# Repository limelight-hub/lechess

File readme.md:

# Lechess
- An early prototyping for smart chess board.

**[Please refer to our planning](https://docs.google.com/spreadsheets/d/1tzjvebM3ZJ8TDiEOB72k3z0SsBjHDWrlPy9oBXgbvGs/edit?gid=1570832848#gid=1570832848)**

****

Figure 1: Hardware block diagram

****

Figure 2: System diagram

# LeChess Functionalities
**1. User Authentication**

    Login: Allows users to log in to the app using their credentials (e.g., email and password). The app sends a request to the NodeJS server, which authenticates the user and provides a JWT token.
    Register: Allows new users to create an account. The account data (username, email, password, etc.) is stored in the NodeJS server and MongoDB.
    Logout: Allows users to log out of the app, clearing their session data.
    Password Reset: Enables users to reset their password via email or SMS by sending a request to the NodeJS server.

**2. Online Mode (App-Only Mode)**

These functions are available when the user is online and connected to the NodeJS server:

*2.1. Play with Computer*

    Start New Game: Users can start a new game against a cloud-based chess engine (e.g., Stockfish).
    Make Move: Users can make a move, and the app sends the move to the NodeJS server to be processed by the chess engine.
    Receive Move: The app receives the move from the chess engine and updates the board.
    Offer Draw/Resign: Users can offer a draw or resign during gameplay.
    Game Over: Displays the result of the game once it's finished (win/loss/draw), and save pgn to database

*2.2. Play with Friend: 2 players*

    Record names of the two players.
    Real-Time Move Updates: The app sends and receives real-time moves from the NodeJS server during a multiplayer game.
    Game Over: Displays the result when the game is finished, and save pgn to database

*2.3. Puzzle Mode*

    Select Puzzle: Users can choose chess puzzles from the server (e.g., checkmate in 2, etc.).
    Solve Puzzle: The app displays the puzzle, and users try to solve it by making moves. The NodeJS server verifies whether the solution is correct.
    Hints: Users can request hints from the server if needed.

*2.4. PGN File Visualization*

    Choose PGN: choose a match from the matches the user played before.
    View PGN: The app reads the PGN file and displays the game on the chessboard for the user to review.
    Step Through Game: Users can move forward and backward.

**3. Bluetooth Mode (Using the Physical Chessboard)**

These functions are available when the user is connected to the physical chessboard via Bluetooth and the Flask server on the Raspberry Pi:

*3.1. Play with Computer* 

    Start New Game: Users can start a new game against a local Stockfish on Raspberry Pi.
    Make Move on Physical Board: The physical chessboard detects the user's move and sends the move to the app over Bluetooth.
    Receive bot Move: The Raspberry Pi processes the move via the chess engine and sends the bot's move back to the app and the physical board and give the pcb led data to light the move up.
    Recommend Move: Moves recommended by the bot will be prcessed to LED data to be lighten up on the board.
    Game Over: Displays the result of the game (win/loss/draw) once it’s finished, and save pgn to database.

*3.2. Play with Friend (Over the Board)*

    Start New Game: Users can start a new game against a friend on the physical chessboard.
    Real-Time Move Detection: The app updates the game state as moves are detected from the chessboard.
    Recommend Move: Moves recommended by the bot will be prcessed to LED data to be lighten up on the board.
    Game Over: Displays the result when the game is finished and saves the game locally on the app or syncs it to the cloud, and save pgn to database.

*3.3. PGN File Visualization*

    Choose PGN: choose a match from a matches list the user have played before using the phone.
    Raspberry Pi server processed PGN and output LED data.
    User can choose to go forward on their phone, or set an automatic mode to go to next move every certain amount of time.

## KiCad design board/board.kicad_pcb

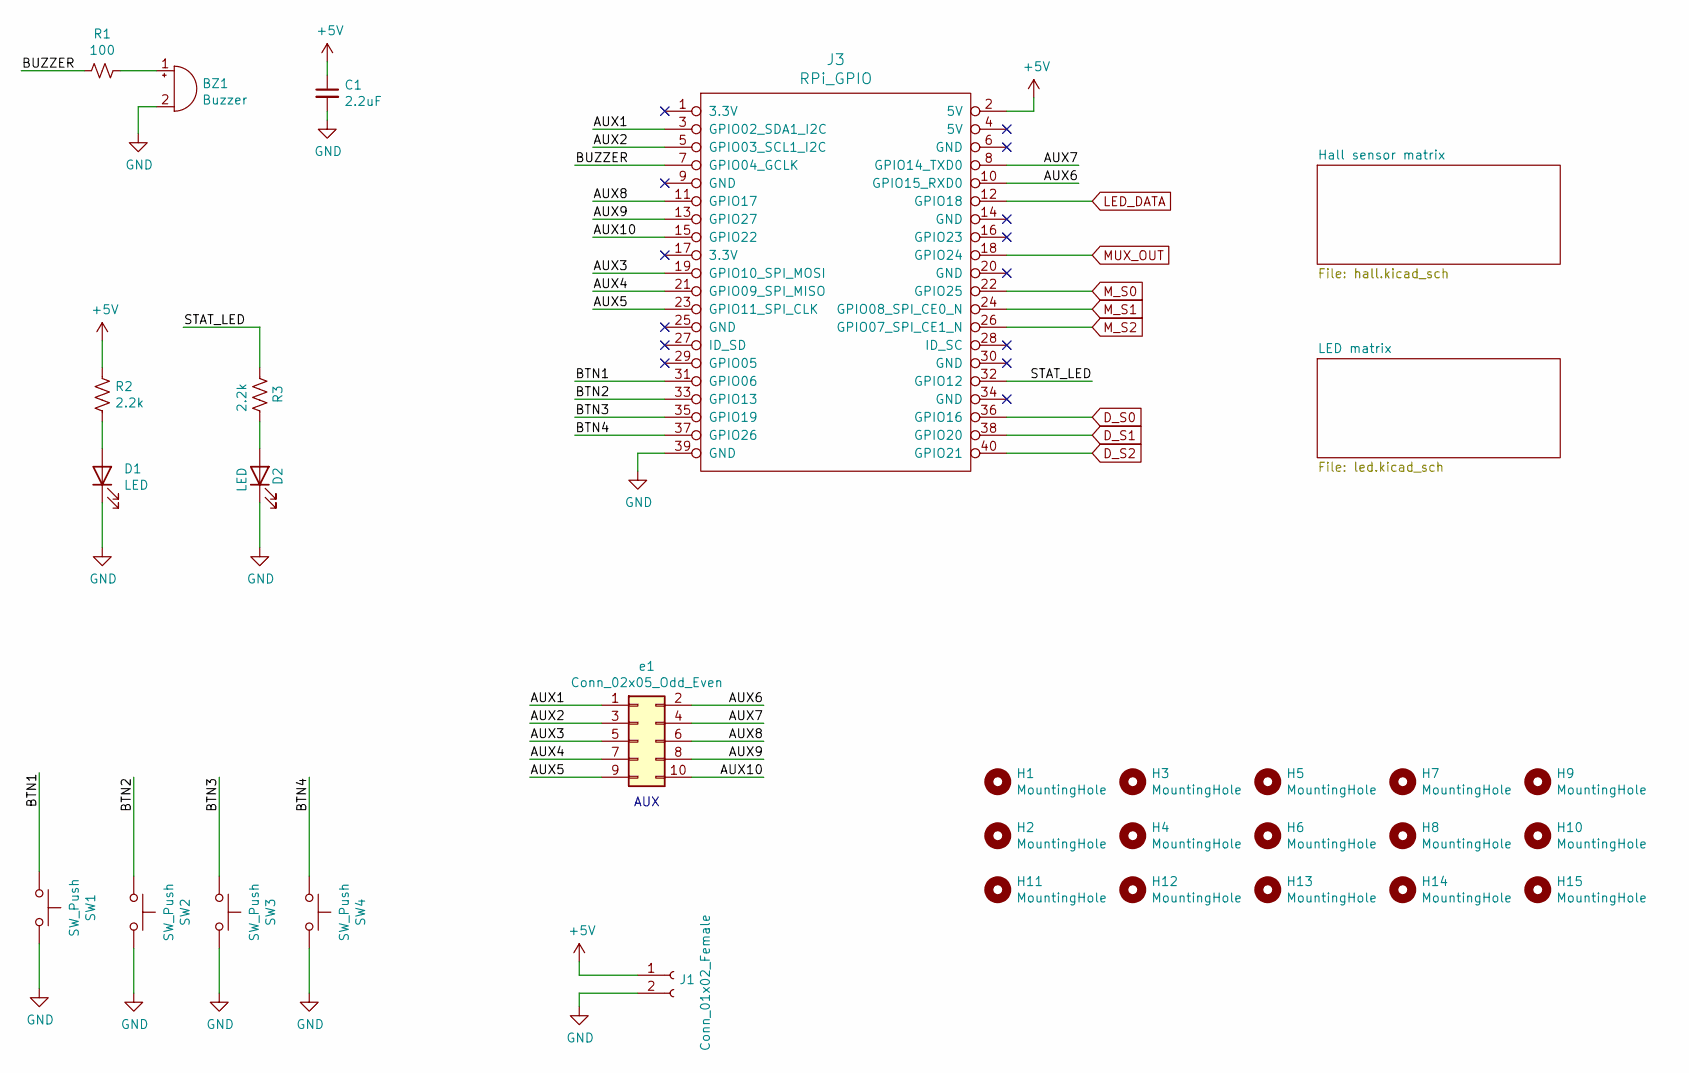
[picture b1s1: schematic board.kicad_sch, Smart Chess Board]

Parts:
BZ1: Buzzer; MagneticBuzzer_ProSignal_ABT-410-RC
C1: 2.2uF; C_0805_2012Metric_Pad1.18x1.45mm_HandSolder
D1, D2: LED; LED_D5.0mm
H1, H2, H3, H4, H5, H6, H7, H8, H9, H10, H11, H12, H13, H14, H15: MountingHole; MountingHole_2.2mm_M2
J1: Conn_01x02_Female; JST_XH_B2B-XH-A_1x02_P2.50mm_Vertical
J3: RPi_GPIO; raspberry_pi_socket
R1: 100; R_Axial_DIN0207_L6.3mm_D2.5mm_P10.16mm_Horizontal
R2, R3: 2.2k; R_Axial_DIN0207_L6.3mm_D2.5mm_P10.16mm_Horizontal
SW1, SW2, SW3, SW4: SW_Push; SW_PUSH_6mm_H5mm
e1: Conn_02x05_Odd_Even; PinSocket_2x05_P2.54mm_Vertical

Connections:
+5V: C1.1, J1.1, J3.2 (5V), R2.1; also elsewhere on the board
/AUX1: J3.3 (GPIO02_SDA1_I2C), e1.1
/AUX2: J3.5 (GPIO03_SCL1_I2C), e1.3
/AUX3: J3.19 (GPIO10_SPI_MOSI), e1.5
/AUX4: J3.21 (GPIO09_SPI_MISO), e1.7
/AUX5: J3.23 (GPIO11_SPI_CLK), e1.9
/AUX6: J3.10 (GPIO15_RXD0), e1.2
/AUX7: J3.8 (GPIO14_TXD0), e1.4
/AUX8: J3.11 (GPIO17), e1.6
/AUX9: J3.13 (GPIO27), e1.8
/AUX10: J3.15 (GPIO22), e1.10
/BTN1: J3.31 (GPIO06), SW1.1
/BTN2: J3.33 (GPIO13), SW2.1
/BTN3: J3.35 (GPIO19), SW3.1
/BTN4: J3.37 (GPIO26), SW4.1
/BUZZER: J3.7 (GPIO04_GCLK), R1.2
/STAT_LED: J3.32 (GPIO12), R3.1
D_S0: J3.36 (GPIO16); also elsewhere on the board
D_S1: J3.38 (GPIO20); also elsewhere on the board
D_S2: J3.40 (GPIO21); also elsewhere on the board
GND: BZ1.2 (+), C1.2, D1.1 (K), D2.1 (K), J1.2, J3.39 (GND), SW1.2, SW2.2, SW3.2, SW4.2; also elsewhere on the board
LED_DATA: J3.12 (GPIO18); also elsewhere on the board
MUX_OUT: J3.18 (GPIO24); also elsewhere on the board
M_S0: J3.22 (GPIO25); also elsewhere on the board
M_S1: J3.24 (GPIO08_SPI_CE0_N); also elsewhere on the board
M_S2: J3.26 (GPIO07_SPI_CE1_N); also elsewhere on the board
unnamed: BZ1.1 (-), R1.1
unnamed: D1.2 (A), R2.2
unnamed: D2.2 (A), R3.2

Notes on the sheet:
AUX

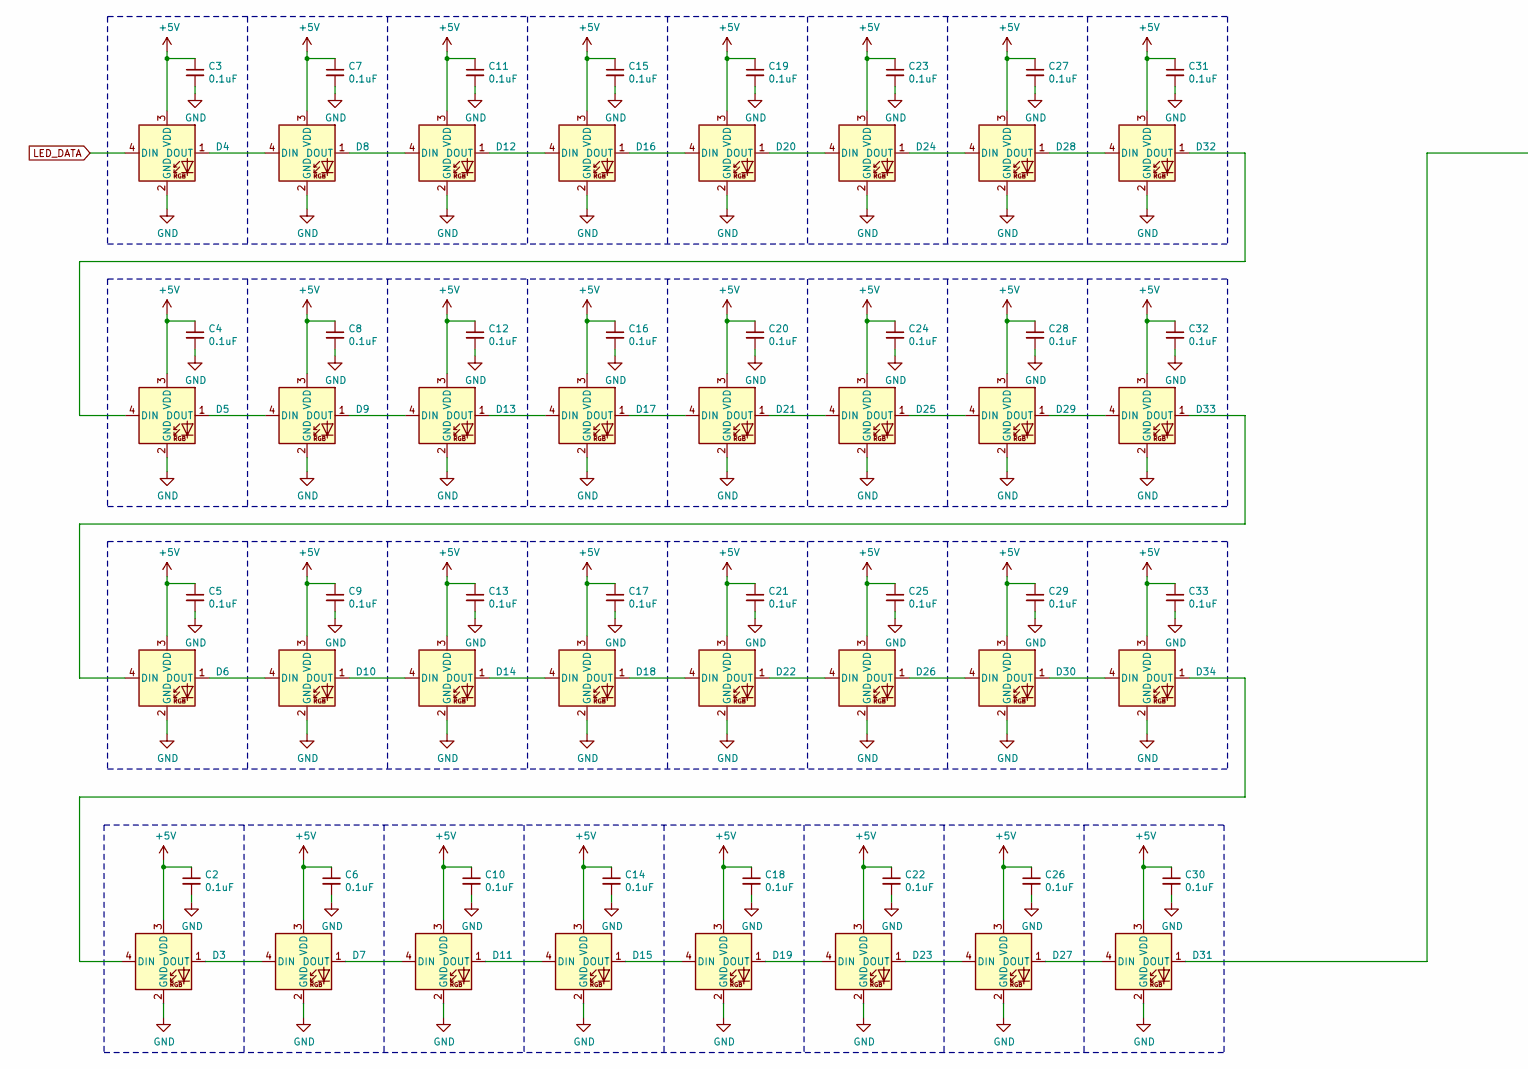
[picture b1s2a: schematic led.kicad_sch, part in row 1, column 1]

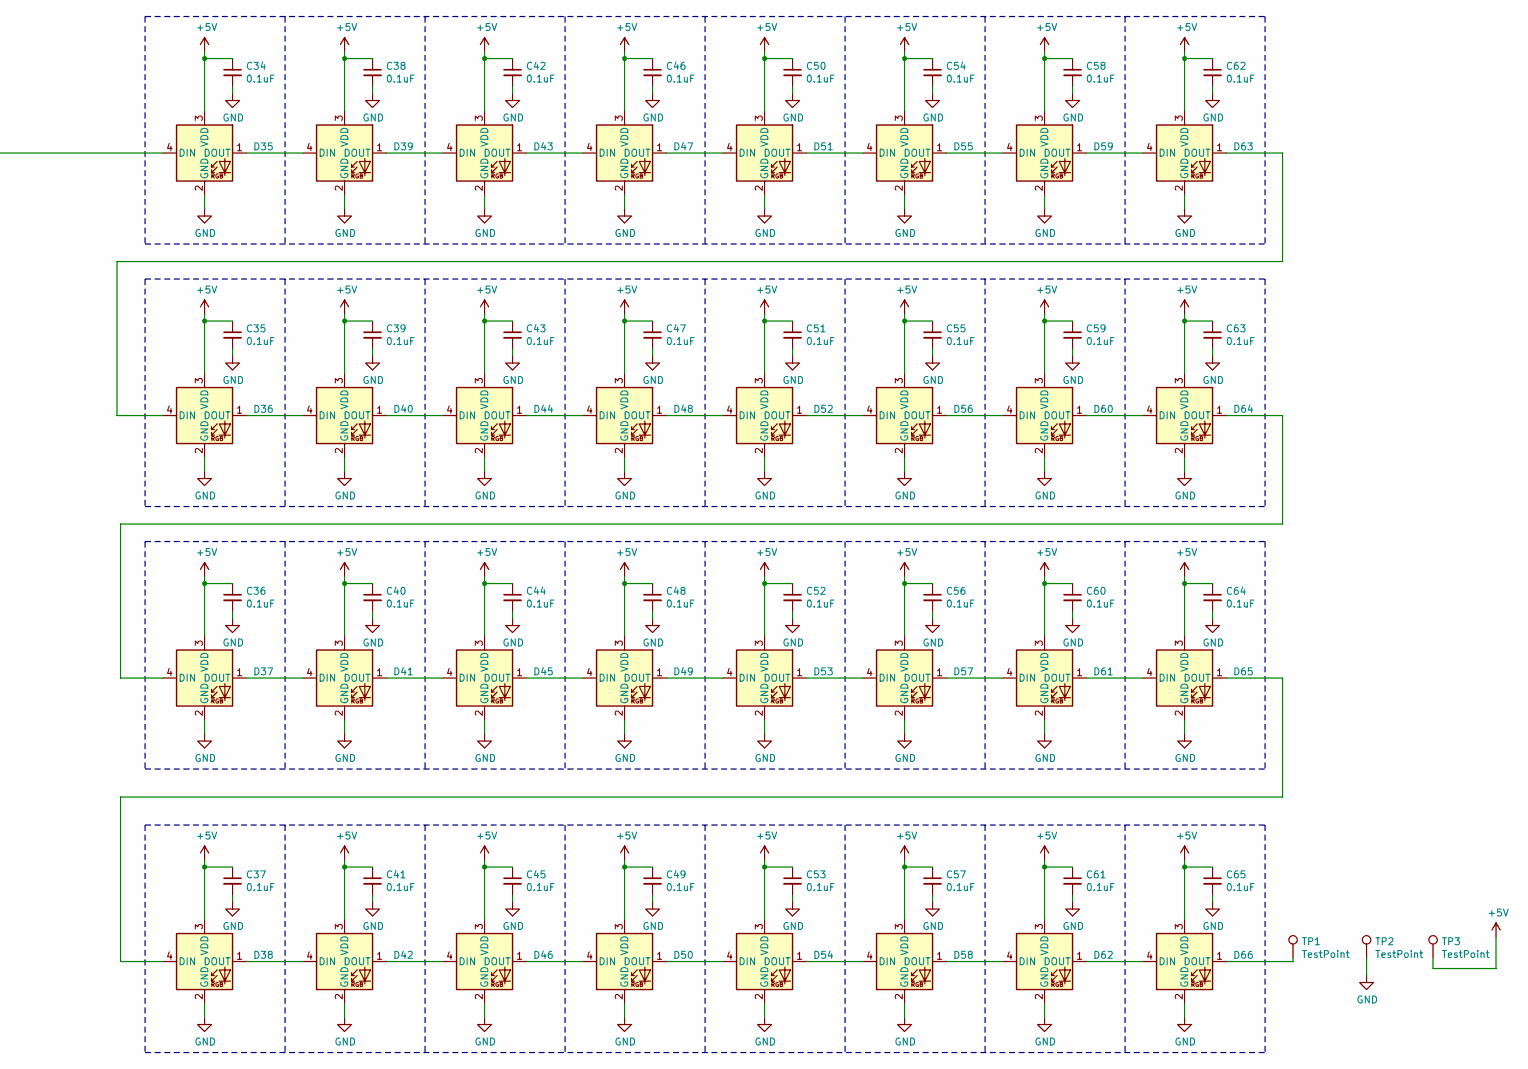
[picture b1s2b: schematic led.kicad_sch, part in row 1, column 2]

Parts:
C2, C3, C4, C5, C6, C7, C8, C9, C10, C11, C12, C13, C14, C15, C16, C17, C18, C19, C20, C21, C22, C23, C24, C25, C26, C27, C28, C29, C30, C31, C32, C33, C34, C35, C36, C37, C38, C39, C40, C41, C42, C43, C44, C45, C46, C47, C48, C49, C50, C51, C52, C53, C54, C55, C56, C57, C58, C59, C60, C61, C62, C63, C64, C65: 0.1uF; C_0805_2012Metric_Pad1.15x1.40mm_HandSolder
D3, D4, D5, D6, D7, D8, D9, D10, D11, D12, D13, D14, D15, D16, D17, D18, D19, D20, D21, D22, D23, D24, D25, D26, D27, D28, D29, D30, D31, D32, D33, D34, D35, D36, D37, D38, D39, D40, D41, D42, D43, D44, D45, D46, D47, D48, D49, D50, D51, D52, D53, D54, D55, D56, D57, D58, D59, D60, D61, D62, D63, D64, D65, D66: WS2812B; LED_WS2812B_PLCC4_5.0x5.0mm_P3.2mm
TP1, TP2, TP3: TestPoint; TestPoint_Pad_2.0x2.0mm

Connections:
+5V: C2.1, C3.1, C4.1, C5.1, C6.1, C7.1, C8.1, C9.1, C10.1, C11.1, C12.1, C13.1, C14.1, C15.1, C16.1, C17.1, C18.1, C19.1, C20.1, C21.1, C22.1, C23.1, C24.1, C25.1, C26.1, C27.1, C28.1, C29.1, C30.1, C31.1, C32.1, C33.1, C34.1, C35.1, C36.1, C37.1, C38.1, C39.1, C40.1, C41.1, C42.1, C43.1, C44.1, C45.1, C46.1, C47.1, C48.1, C49.1, C50.1, C51.1, C52.1, C53.1, C54.1, C55.1, C56.1, C57.1, C58.1, C59.1, C60.1, C61.1, C62.1, C63.1, C64.1, C65.1, D3.3 (VDD), D4.3 (VDD), D5.3 (VDD), D6.3 (VDD), D7.3 (VDD), D8.3 (VDD), D9.3 (VDD), D10.3 (VDD), D11.3 (VDD), D12.3 (VDD), D13.3 (VDD), D14.3 (VDD), D15.3 (VDD), D16.3 (VDD), D17.3 (VDD), D18.3 (VDD), D19.3 (VDD), D20.3 (VDD), D21.3 (VDD), D22.3 (VDD), D23.3 (VDD), D24.3 (VDD), D25.3 (VDD), D26.3 (VDD), D27.3 (VDD), D28.3 (VDD), D29.3 (VDD), D30.3 (VDD), D31.3 (VDD), D32.3 (VDD), D33.3 (VDD), D34.3 (VDD), D35.3 (VDD), D36.3 (VDD), D37.3 (VDD), D38.3 (VDD), D39.3 (VDD), D40.3 (VDD), D41.3 (VDD), D42.3 (VDD), D43.3 (VDD), D44.3 (VDD), D45.3 (VDD), D46.3 (VDD), D47.3 (VDD), D48.3 (VDD), D49.3 (VDD), D50.3 (VDD), D51.3 (VDD), D52.3 (VDD), D53.3 (VDD), D54.3 (VDD), D55.3 (VDD), D56.3 (VDD), D57.3 (VDD), D58.3 (VDD), D59.3 (VDD), D60.3 (VDD), D61.3 (VDD), D62.3 (VDD), D63.3 (VDD), D64.3 (VDD), D65.3 (VDD), D66.3 (VDD), TP3.1; also elsewhere on the board
GND: C2.2, C3.2, C4.2, C5.2, C6.2, C7.2, C8.2, C9.2, C10.2, C11.2, C12.2, C13.2, C14.2, C15.2, C16.2, C17.2, C18.2, C19.2, C20.2, C21.2, C22.2, C23.2, C24.2, C25.2, C26.2, C27.2, C28.2, C29.2, C30.2, C31.2, C32.2, C33.2, C34.2, C35.2, C36.2, C37.2, C38.2, C39.2, C40.2, C41.2, C42.2, C43.2, C44.2, C45.2, C46.2, C47.2, C48.2, C49.2, C50.2, C51.2, C52.2, C53.2, C54.2, C55.2, C56.2, C57.2, C58.2, C59.2, C60.2, C61.2, C62.2, C63.2, C64.2, C65.2, D3.2 (GND), D4.2 (GND), D5.2 (GND), D6.2 (GND), D7.2 (GND), D8.2 (GND), D9.2 (GND), D10.2 (GND), D11.2 (GND), D12.2 (GND), D13.2 (GND), D14.2 (GND), D15.2 (GND), D16.2 (GND), D17.2 (GND), D18.2 (GND), D19.2 (GND), D20.2 (GND), D21.2 (GND), D22.2 (GND), D23.2 (GND), D24.2 (GND), D25.2 (GND), D26.2 (GND), D27.2 (GND), D28.2 (GND), D29.2 (GND), D30.2 (GND), D31.2 (GND), D32.2 (GND), D33.2 (GND), D34.2 (GND), D35.2 (GND), D36.2 (GND), D37.2 (GND), D38.2 (GND), D39.2 (GND), D40.2 (GND), D41.2 (GND), D42.2 (GND), D43.2 (GND), D44.2 (GND), D45.2 (GND), D46.2 (GND), D47.2 (GND), D48.2 (GND), D49.2 (GND), D50.2 (GND), D51.2 (GND), D52.2 (GND), D53.2 (GND), D54.2 (GND), D55.2 (GND), D56.2 (GND), D57.2 (GND), D58.2 (GND), D59.2 (GND), D60.2 (GND), D61.2 (GND), D62.2 (GND), D63.2 (GND), D64.2 (GND), D65.2 (GND), D66.2 (GND), TP2.1; also elsewhere on the board
LED_DATA: D4.4 (DIN); also elsewhere on the board
unnamed: D3.1 (DOUT), D7.4 (DIN)
unnamed: D3.4 (DIN), D34.1 (DOUT)
unnamed: D4.1 (DOUT), D8.4 (DIN)
unnamed: D5.1 (DOUT), D9.4 (DIN)
unnamed: D10.1 (DOUT), D14.4 (DIN)
unnamed: D6.1 (DOUT), D10.4 (DIN)
unnamed: D11.1 (DOUT), D15.4 (DIN)
unnamed: D7.1 (DOUT), D11.4 (DIN)
unnamed: D12.1 (DOUT), D16.4 (DIN)
unnamed: D8.1 (DOUT), D12.4 (DIN)
unnamed: D13.1 (DOUT), D17.4 (DIN)
unnamed: D9.1 (DOUT), D13.4 (DIN)
unnamed: D14.1 (DOUT), D18.4 (DIN)
unnamed: D15.1 (DOUT), D19.4 (DIN)
unnamed: D16.1 (DOUT), D20.4 (DIN)
unnamed: D17.1 (DOUT), D21.4 (DIN)
unnamed: D18.1 (DOUT), D22.4 (DIN)
unnamed: D19.1 (DOUT), D23.4 (DIN)
unnamed: D20.1 (DOUT), D24.4 (DIN)
unnamed: D21.1 (DOUT), D25.4 (DIN)
unnamed: D22.1 (DOUT), D26.4 (DIN)
unnamed: D23.1 (DOUT), D27.4 (DIN)
unnamed: D24.1 (DOUT), D28.4 (DIN)
unnamed: D25.1 (DOUT), D29.4 (DIN)
unnamed: D26.1 (DOUT), D30.4 (DIN)
unnamed: D27.1 (DOUT), D31.4 (DIN)
unnamed: D28.1 (DOUT), D32.4 (DIN)
unnamed: D29.1 (DOUT), D33.4 (DIN)
unnamed: D30.1 (DOUT), D34.4 (DIN)
unnamed: D31.1 (DOUT), D35.4 (DIN)
unnamed: D5.4 (DIN), D32.1 (DOUT)
unnamed: D6.4 (DIN), D33.1 (DOUT)
unnamed: D35.1 (DOUT), D39.4 (DIN)
unnamed: D36.1 (DOUT), D40.4 (DIN)
unnamed: D36.4 (DIN), D63.1 (DOUT)
unnamed: D37.1 (DOUT), D41.4 (DIN)
unnamed: D37.4 (DIN), D64.1 (DOUT)
unnamed: D38.1 (DOUT), D42.4 (DIN)
unnamed: D38.4 (DIN), D65.1 (DOUT)
unnamed: D39.1 (DOUT), D43.4 (DIN)
unnamed: D40.1 (DOUT), D44.4 (DIN)
unnamed: D41.1 (DOUT), D45.4 (DIN)
unnamed: D42.1 (DOUT), D46.4 (DIN)
unnamed: D43.1 (DOUT), D47.4 (DIN)
unnamed: D44.1 (DOUT), D48.4 (DIN)
unnamed: D45.1 (DOUT), D49.4 (DIN)
unnamed: D46.1 (DOUT), D50.4 (DIN)
unnamed: D47.1 (DOUT), D51.4 (DIN)
unnamed: D48.1 (DOUT), D52.4 (DIN)
unnamed: D49.1 (DOUT), D53.4 (DIN)
unnamed: D50.1 (DOUT), D54.4 (DIN)
unnamed: D51.1 (DOUT), D55.4 (DIN)
unnamed: D52.1 (DOUT), D56.4 (DIN)
unnamed: D53.1 (DOUT), D57.4 (DIN)
unnamed: D54.1 (DOUT), D58.4 (DIN)
unnamed: D55.1 (DOUT), D59.4 (DIN)
unnamed: D56.1 (DOUT), D60.4 (DIN)
unnamed: D57.1 (DOUT), D61.4 (DIN)
unnamed: D58.1 (DOUT), D62.4 (DIN)
unnamed: D59.1 (DOUT), D63.4 (DIN)
unnamed: D60.1 (DOUT), D64.4 (DIN)
unnamed: D61.1 (DOUT), D65.4 (DIN)
unnamed: D62.1 (DOUT), D66.4 (DIN)
unnamed: D66.1 (DOUT), TP1.1

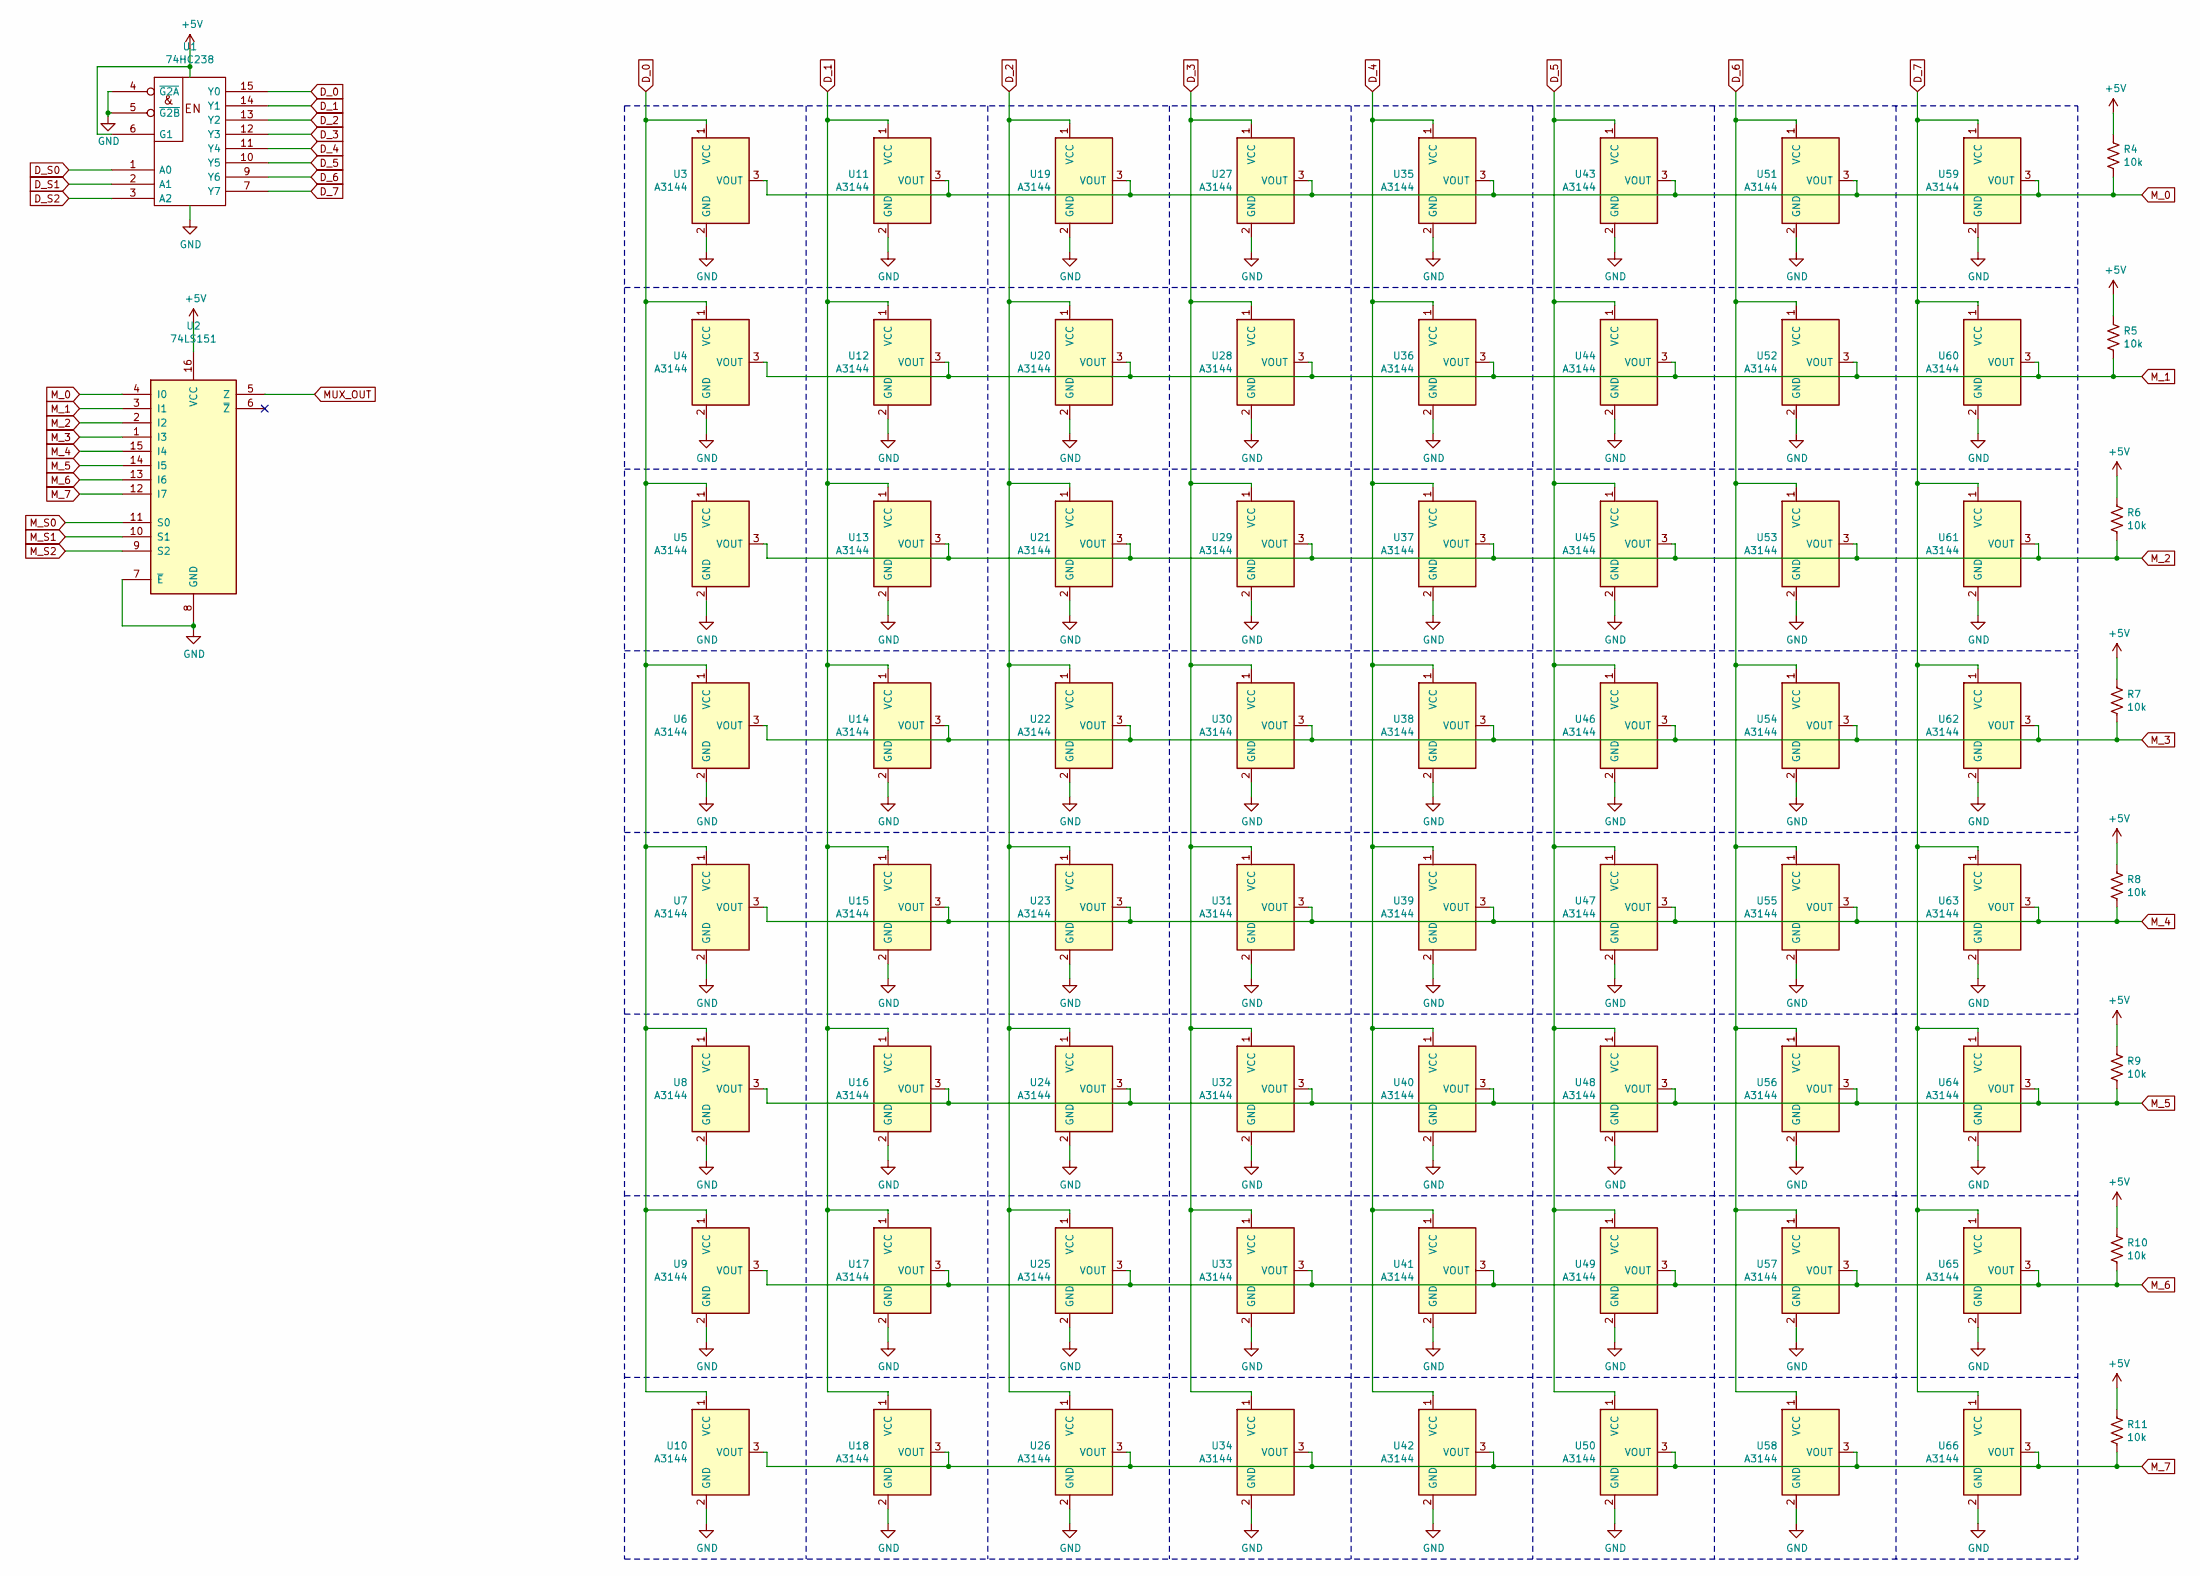
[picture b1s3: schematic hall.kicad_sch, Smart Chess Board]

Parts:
R4, R5, R6, R7, R8, R9, R10, R11: 10k; R_0805_2012Metric_Pad1.15x1.40mm_HandSolder
U1: 74HC238; DIP-16_W7.62mm
U2: 74LS151; DIP-16_W7.62mm
U3, U4, U5, U6, U7, U8, U9, U10, U11, U12, U13, U14, U15, U16, U17, U18, U19, U20, U21, U22, U23, U24, U25, U26, U27, U28, U29, U30, U31, U32, U33, U34, U35, U36, U37, U38, U39, U40, U41, U42, U43, U44, U45, U46, U47, U48, U49, U50, U51, U52, U53, U54, U55, U56, U57, U58, U59, U60, U61, U62, U63, U64, U65, U66: A3144; TO-92Flat

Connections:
+5V: R4.1, R5.1, R6.1, R7.1, R8.1, R9.1, R10.1, R11.1, U1.6 (G1), U1.16 (VCC), U2.16 (VCC); also elsewhere on the board
D_0: U1.15 (Y0), U3.1 (VCC), U4.1 (VCC), U5.1 (VCC), U6.1 (VCC), U7.1 (VCC), U8.1 (VCC), U9.1 (VCC), U10.1 (VCC)
D_1: U1.14 (Y1), U11.1 (VCC), U12.1 (VCC), U13.1 (VCC), U14.1 (VCC), U15.1 (VCC), U16.1 (VCC), U17.1 (VCC), U18.1 (VCC)
D_2: U1.13 (Y2), U19.1 (VCC), U20.1 (VCC), U21.1 (VCC), U22.1 (VCC), U23.1 (VCC), U24.1 (VCC), U25.1 (VCC), U26.1 (VCC)
D_3: U1.12 (Y3), U27.1 (VCC), U28.1 (VCC), U29.1 (VCC), U30.1 (VCC), U31.1 (VCC), U32.1 (VCC), U33.1 (VCC), U34.1 (VCC)
D_4: U1.11 (Y4), U35.1 (VCC), U36.1 (VCC), U37.1 (VCC), U38.1 (VCC), U39.1 (VCC), U40.1 (VCC), U41.1 (VCC), U42.1 (VCC)
D_5: U1.10 (Y5), U43.1 (VCC), U44.1 (VCC), U45.1 (VCC), U46.1 (VCC), U47.1 (VCC), U48.1 (VCC), U49.1 (VCC), U50.1 (VCC)
D_6: U1.9 (Y6), U51.1 (VCC), U52.1 (VCC), U53.1 (VCC), U54.1 (VCC), U55.1 (VCC), U56.1 (VCC), U57.1 (VCC), U58.1 (VCC)
D_7: U1.7 (Y7), U59.1 (VCC), U60.1 (VCC), U61.1 (VCC), U62.1 (VCC), U63.1 (VCC), U64.1 (VCC), U65.1 (VCC), U66.1 (VCC)
D_S0: U1.1 (A0); also elsewhere on the board
D_S1: U1.2 (A1); also elsewhere on the board
D_S2: U1.3 (A2); also elsewhere on the board
GND: U1.4 (~G2A), U1.5 (~G2B), U1.8 (GND), U2.7 (~E), U2.8 (GND), U3.2 (GND), U4.2 (GND), U5.2 (GND), U6.2 (GND), U7.2 (GND), U8.2 (GND), U9.2 (GND), U10.2 (GND), U11.2 (GND), U12.2 (GND), U13.2 (GND), U14.2 (GND), U15.2 (GND), U16.2 (GND), U17.2 (GND), U18.2 (GND), U19.2 (GND), U20.2 (GND), U21.2 (GND), U22.2 (GND), U23.2 (GND), U24.2 (GND), U25.2 (GND), U26.2 (GND), U27.2 (GND), U28.2 (GND), U29.2 (GND), U30.2 (GND), U31.2 (GND), U32.2 (GND), U33.2 (GND), U34.2 (GND), U35.2 (GND), U36.2 (GND), U37.2 (GND), U38.2 (GND), U39.2 (GND), U40.2 (GND), U41.2 (GND), U42.2 (GND), U43.2 (GND), U44.2 (GND), U45.2 (GND), U46.2 (GND), U47.2 (GND), U48.2 (GND), U49.2 (GND), U50.2 (GND), U51.2 (GND), U52.2 (GND), U53.2 (GND), U54.2 (GND), U55.2 (GND), U56.2 (GND), U57.2 (GND), U58.2 (GND), U59.2 (GND), U60.2 (GND), U61.2 (GND), U62.2 (GND), U63.2 (GND), U64.2 (GND), U65.2 (GND), U66.2 (GND); also elsewhere on the board
MUX_OUT: U2.5 (Z); also elsewhere on the board
M_0: R4.2, U2.4 (I0), U3.3 (VOUT), U11.3 (VOUT), U19.3 (VOUT), U27.3 (VOUT), U35.3 (VOUT), U43.3 (VOUT), U51.3 (VOUT), U59.3 (VOUT)
M_1: R5.2, U2.3 (I1), U4.3 (VOUT), U12.3 (VOUT), U20.3 (VOUT), U28.3 (VOUT), U36.3 (VOUT), U44.3 (VOUT), U52.3 (VOUT), U60.3 (VOUT)
M_2: R6.2, U2.2 (I2), U5.3 (VOUT), U13.3 (VOUT), U21.3 (VOUT), U29.3 (VOUT), U37.3 (VOUT), U45.3 (VOUT), U53.3 (VOUT), U61.3 (VOUT)
M_3: R7.2, U2.1 (I3), U6.3 (VOUT), U14.3 (VOUT), U22.3 (VOUT), U30.3 (VOUT), U38.3 (VOUT), U46.3 (VOUT), U54.3 (VOUT), U62.3 (VOUT)
M_4: R8.2, U2.15 (I4), U7.3 (VOUT), U15.3 (VOUT), U23.3 (VOUT), U31.3 (VOUT), U39.3 (VOUT), U47.3 (VOUT), U55.3 (VOUT), U63.3 (VOUT)
M_5: R9.2, U2.14 (I5), U8.3 (VOUT), U16.3 (VOUT), U24.3 (VOUT), U32.3 (VOUT), U40.3 (VOUT), U48.3 (VOUT), U56.3 (VOUT), U64.3 (VOUT)
M_6: R10.2, U2.13 (I6), U9.3 (VOUT), U17.3 (VOUT), U25.3 (VOUT), U33.3 (VOUT), U41.3 (VOUT), U49.3 (VOUT), U57.3 (VOUT), U65.3 (VOUT)
M_7: R11.2, U2.12 (I7), U10.3 (VOUT), U18.3 (VOUT), U26.3 (VOUT), U34.3 (VOUT), U42.3 (VOUT), U50.3 (VOUT), U58.3 (VOUT), U66.3 (VOUT)
M_S0: U2.11 (S0); also elsewhere on the board
M_S1: U2.10 (S1); also elsewhere on the board
M_S2: U2.9 (S2); also elsewhere on the board

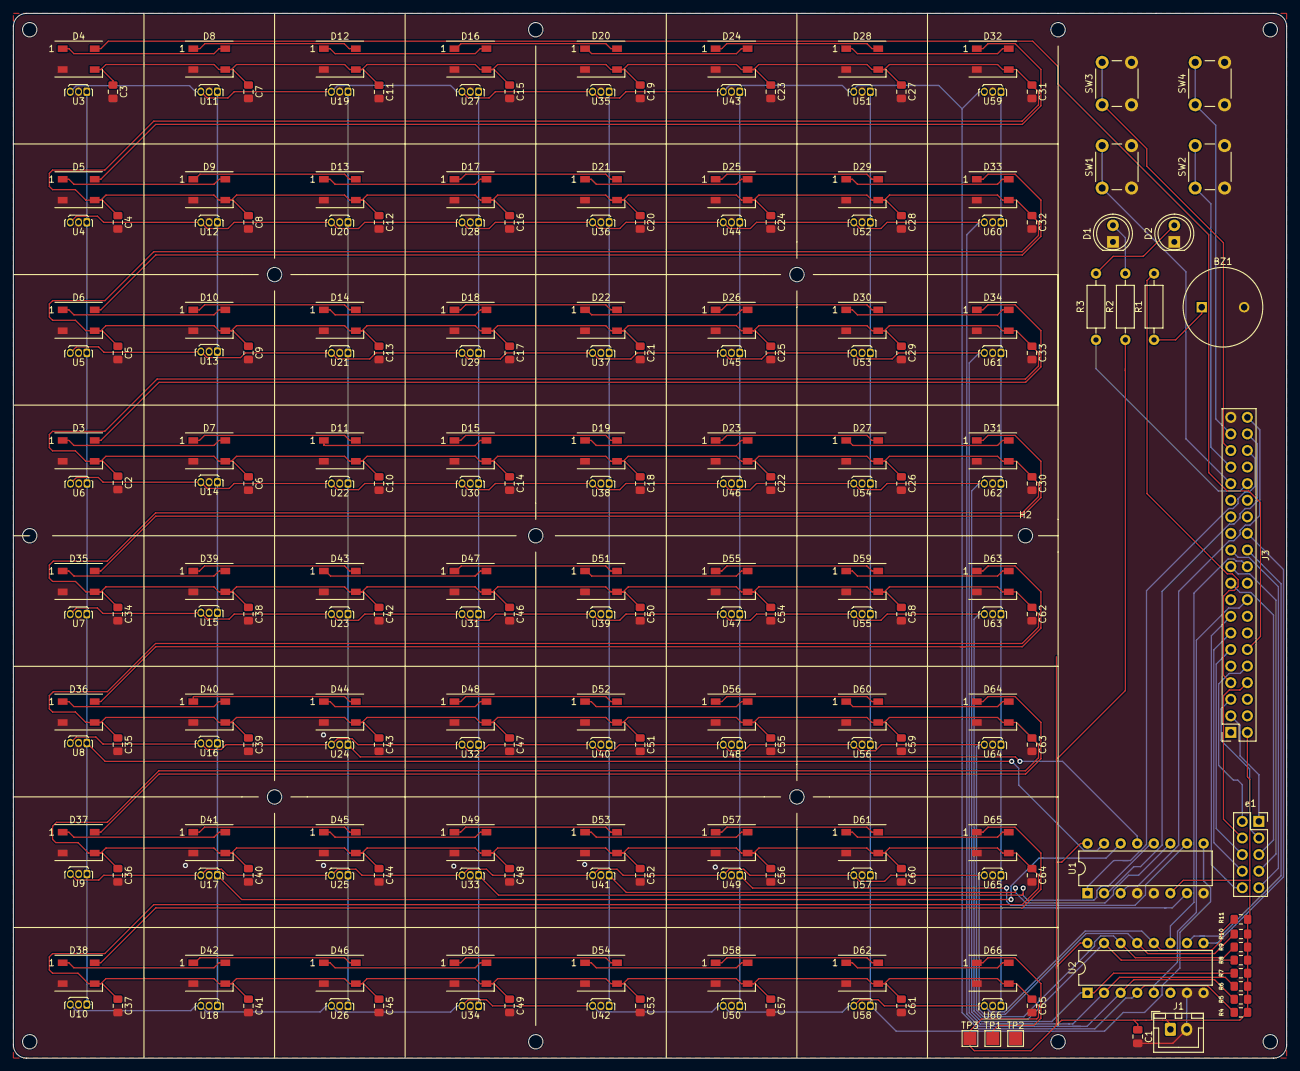
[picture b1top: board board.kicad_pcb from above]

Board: 2 copper layers, 195.0 x 160.0 mm, 234 parts (0 on the bottom side), 109 nets.

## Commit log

2024-10-17 innitial commit
